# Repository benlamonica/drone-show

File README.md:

# drone-show
The code used for my amateur drone show quad-copters

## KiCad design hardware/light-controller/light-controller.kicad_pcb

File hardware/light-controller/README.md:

# Light controller

A 73 x 35 mm, 2-layer board that slides into the frame's light rail
(`frame/out/light_pcb_outline.dxf`). It hosts the Wi-Fi link and drives twelve 1 W-class
Cree XP-E2 LEDs (3 red, 3 green, 3 blue, 3 white) straight from a 4S-6S pack.

| | |
|---|---|
| MCU | RP2350A (QFN-60) + 2 MB W25Q16 flash, 12 MHz crystal |
| Wi-Fi | Raspberry Pi RM2 module (CYW43439), wired exactly like the Pico 2 W |
| LED drive | 4 x AL8860 hysteretic constant-current bucks, one per colour, 0.67 A each |
| LEDs | 12 x XP-E2 on the bottom side, facing the diffuser |
| Input | 4S-6S (12-26 V), reverse-polarity P-FET, SMBJ26A TVS |
| Logic supply | LMR51420 buck to 3.3 V |
| Interfaces | JST-SH UART to the flight controller, SWD and spares on 7 pogo-pin test pads |
| Board | 2 layers, 1.6 mm, 1 oz, smallest passive 0603, PCBWay standard rules |

## Files

| Path | What |
|---|---|
| `light-controller.kicad_pro/.kicad_sch/.kicad_pcb` | KiCad project (opens in KiCad 7 and later) |
| `light-controller.kicad_dru` | PCBWay design rules (loaded by DRC automatically) |
| `lightctl.kicad_sym`, `lightctl.pretty/` | Project-local symbols and footprints, nothing from global libraries |
| `fab/light-controller-gerbers.zip` | Upload this to PCBWay |
| `fab/light-controller-bom.csv`, `fab/light-controller-cpl.csv` | PCBWay assembly BOM and placement (both sides) |
| `images/` | Renders of both sides |
| `tools/` | The generators. `design.py` is the single source of the netlist and BOM |

Regenerate everything: `python3 tools/build_lib.py && python3 tools/gen_sch.py &&
python3 tools/gen_pcb.py`, then route (`tools/route.py`, `tools/finish_route.py`,
`tools/stitch.py`), check (`tools/drc.py`) and export (`tools/gen_fab.py`,
`tools/render.py`). Re-running `gen_pcb.py` throws the routing away, so after the
first build edit the board in KiCad instead.

## Brightness and power

Each colour is a string of three XP-E2 in series on its own AL8860, with the sense
resistor setting I = 0.1 V / 0.15 ohm = 0.67 A. At that current, roughly:

| Colour | Per LED | 3 LEDs |
|---|---|---|
| White (cool) | ~230 lm | ~700 lm |
| Green | ~170 lm | ~500 lm |
| Red | ~100 lm | ~300 lm |
| Blue | ~450 mW radiant | ~1.3 W radiant |

All four channels at full is about 1500 lm and 23 W into the LEDs, roughly 15-17 W of heat. Inside the diffuser the board sits in nearly still air, and a rough estimate is that it can shed only about 5 W continuously before the air inside passes 55-60 C, where a PLA diffuser starts to soften. These are estimates; measure on the bench (below) before setting final limits. The firmware must:

- hold the total LED power to about 5 W averaged over 30 s (roughly 150-200 lm of white, or one colour at about 75 %); short flashes above that are fine,
- read the NTC (`TH1`, on GPIO26), start dimming at 60 C board temperature and reach zero output at 80 C,
- never run full white on the bench without airflow.

The diffuser helps if it is printed in PETG or another plastic rated above 80 C instead of PLA, and if it has vent slots so prop wash moves air across the board (see `frame/`).

Bench test before building all 30: put one board in a diffuser, run it at a fixed power (start at 3 W, then 5 W, then 8 W) for 10 minutes each, and log the NTC temperature. The highest power that stays under 60 C is the real budget; update the numbers above with it.

To trade brightness for heat, change the four 0.15 ohm sense resistors
(`R31`-`R34`): 0.2 ohm gives 0.5 A. Don't go below 0.1 ohm (1 A, the XP-E2 maximum).

Dimming is PWM on each AL8860 CTRL pin through a 1k/10k divider. Keep the PWM under
500 Hz for linear dimming (1 kHz still works but the bottom of the range gets coarse).
CTRL below 0.2 V switches the channel fully off, so the LEDs are dark while the RP2350
is in reset. `C51`-`C54` are not fitted; fit them only to switch to analog dimming.

## Pin map

| GPIO | Function |
|---|---|
| 0 / 1 | UART TX / RX to the flight controller (MAVLink) |
| 2 | PWM green (PWM1 A) |
| 3 | PWM white (PWM1 B) |
| 8 | PWM red (PWM4 A) |
| 9 | PWM blue (PWM4 B) |
| 10, 11, 16 | Spare, on test pads TP2-TP4 |
| 23, 24, 25, 29 | RM2: WL_ON, data, CS, clock (same as Pico 2 W) |
| 26 (ADC0) | NTC board temperature |
| 27 (ADC1) | Battery voltage, 100k/10k divider (x11) |

Because the radio uses the Pico 2 W pins, the stock `pico2_w` board definition and
`pico_cyw43_arch` work unchanged. There is no separate status LED: use the CYW43
`WL_GPIO0` LED (`cyw43_arch_gpio_put(CYW43_WL_GPIO_LED_PIN, ...)`) as on a Pico 2 W, or
the main LEDs themselves. GPIO 4-7, 12-15, 17-22 and 28 are unconnected.

## Programming: pogo pins, no connectors

USB-C, the BOOTSEL button and the SWD connector were left off. All seven test pads sit in
one row on the bottom, 1.5 mm pads at 2.6 mm pitch along y = -13.4 mm, so one pogo-pin
jig reaches them all:

| Pad | x (mm) | Net |
|---|---|---|
| TP4 | -25.4 | GPIO16 |
| TP3 | -22.8 | GPIO11 |
| TP2 | -20.2 | GPIO10 |
| TP1 | -17.6 | RUN |
| TP5 | -15.0 | SWCLK |
| TP6 | -12.4 | GND |
| TP7 | -9.8 | SWDIO |

For the first flash, power the board from the pack and hold a Raspberry Pi Debug Probe
on TP5-TP7 (`openocd -f interface/cmsis-dap.cfg -f target/rp2350.cfg`). After that,
update the firmware over the flight controller UART or Wi-Fi.

Planned, not built yet: field updates use the RP2350 boot ROM's two-slot (A/B) partition
table instead of a custom bootloader. The running app receives a new image over the FC
UART (or Wi-Fi), writes it to the spare slot and reboots. If the new image doesn't
start, the boot ROM falls back to the old one, so a bad update can't brick a drone.

## Firmware port from the existing `pico/` code

The current firmware drives a WS2812B/SK6812 strip through `port/led_strip.c`. On this
board the same `led_strip_fill(r, g, b, w)` call should instead set four PWM levels on
GPIO 8, 2, 9, 3 (red, green, blue, white). The `show_led` MAVLink parser
(`DEBUG_VECT` "rgb") stays as it is. Use about 400 Hz PWM with a gamma table, and add
the power cap and NTC derating described above.

## Things to check before ordering

1. **XP-E2 polarity.** The footprint uses KiCad's `LED_Cree-XP` (pad 1 cathode, pad 2
   anode, centre pad 3 thermal and electrically neutral, tied to GND for heat). Compare
   with the current Cree XP-E2 datasheet drawing.
2. **RM2 footprint.** `RPi_RM2` was drawn from the RM2 datasheet (pads and antenna
   keep-out). Check it against the latest Raspberry Pi drawing; nothing may be placed
   under or in front of the antenna, and the board edge past it is clear of copper.
3. **ERC.** The schematic is generated, so open it in KiCad and run ERC once. The
   netlist was verified to match the board pin for pin.
4. **DRC.** Run DRC in KiCad with the project rules; see the routing notes below.
5. **LED bins.** Any in-stock flux bin works; the MPNs in the BOM are typical ones.

## Routing notes

The board was routed by script (Freerouting, then a grid router with rip-up in
`tools/finish_route.py`, then the `gnd_*` tools to tie every ground pad and pour island
together with stitching vias). Current DRC with `light-controller.kicad_dru`:

- 0 errors: no clearance, hole, width or unconnected items. The netlist on the board was
  checked pad by pad against `tools/design.py`.
- 76 silkscreen warnings (reference text overlapping other silk or clipped by the mask).
  They are cosmetic; tidy the reference text in KiCad if you care about the labels.

The tracks are machine-made and look it: there are short zig-zags and a few long
detours. They are electrically fine. Ground pads use solid (not thermal) pour
connections, so hand soldering ground pins needs a hot iron; reflow is unaffected.
The 0.4 mm-pitch RP2350 fan-out uses 0.15 mm tracks and 0.3/0.6 mm vias, inside
PCBWay's standard 6/6 mil, 0.3 mm process.

## PCBWay order settings

2 layers, FR-4, 1.6 mm, 1 oz outer copper, HASL lead-free or ENIG, min track/space
6/6 mil, min hole 0.3 mm. Assembly on both sides (LEDs, flash, buck and a few
passives are on the bottom). Battery leads are soldered by hand to `J1`.

## Main parts

| Ref | Part | Mouser / maker number |
|---|---|---|
| U2 | RP2350A | Raspberry Pi RP2350A (or RP2354A with built-in flash, then omit U3) |
| M1 | RM2 radio module | Raspberry Pi SC1169 |
| U3 | 16 Mbit QSPI flash | Winbond W25Q16JVSNIQ |
| U1 | 3.3 V buck | TI LMR51420YDDCR |
| L1 | 3.3 V buck inductor, 6.8 uH, 4 x 4 mm | Laird TYA40206R8M-10 (pads also fit Coilcraft XAL4020-682MEC) |
| U5-U8 | LED driver | Diodes AL8860MP-13 |
| L3-L6 | 47 uH 0.92 A | Bourns SRN6028-470M |
| D6-D9 | Schottky | Diodes B240A-13-F |
| R31-R34 | 0.15 ohm sense | Vishay WSL1206R1500FEA |
| LED1-12 | XP-E2 R/G/B/W | Cree XPEBRD, XPEBGR, XPEBBL, XPEBWT |
| Q1 | Reverse-polarity P-FET | Diodes DMP6023LE-13 |
| D2 | TVS | Littelfuse SMBJ26A |

The full list is in `fab/light-controller-bom.csv`.

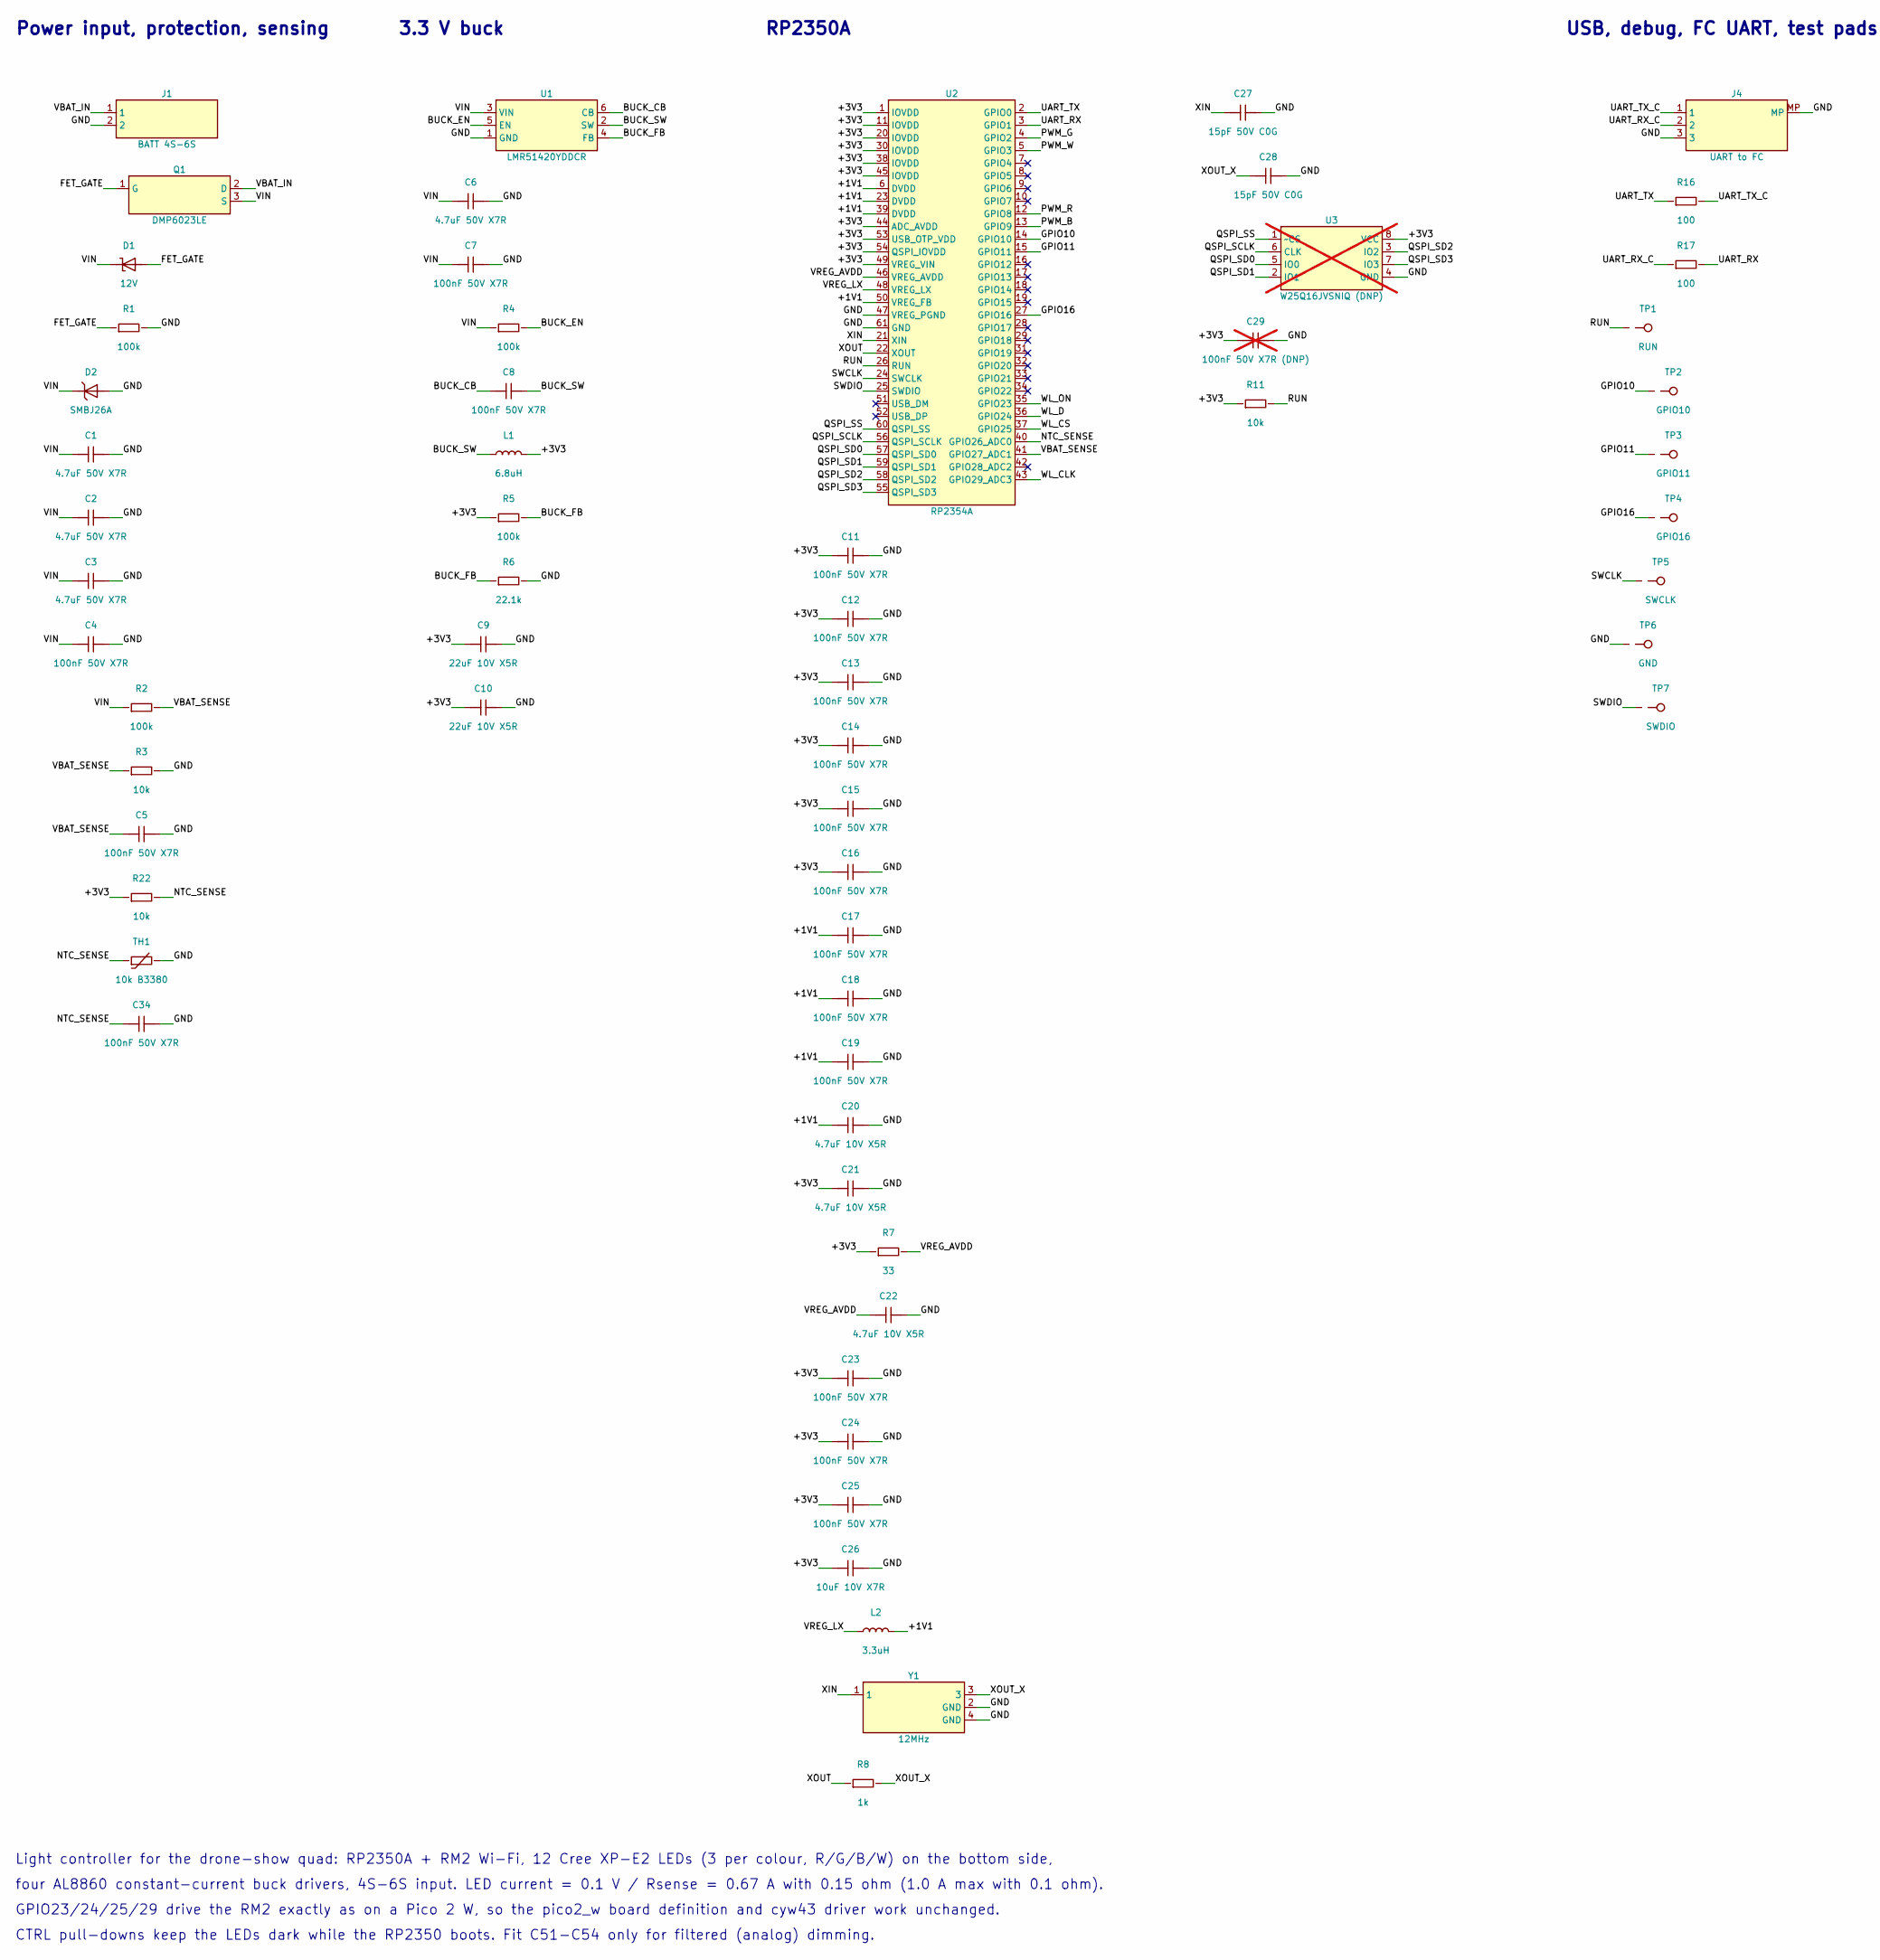
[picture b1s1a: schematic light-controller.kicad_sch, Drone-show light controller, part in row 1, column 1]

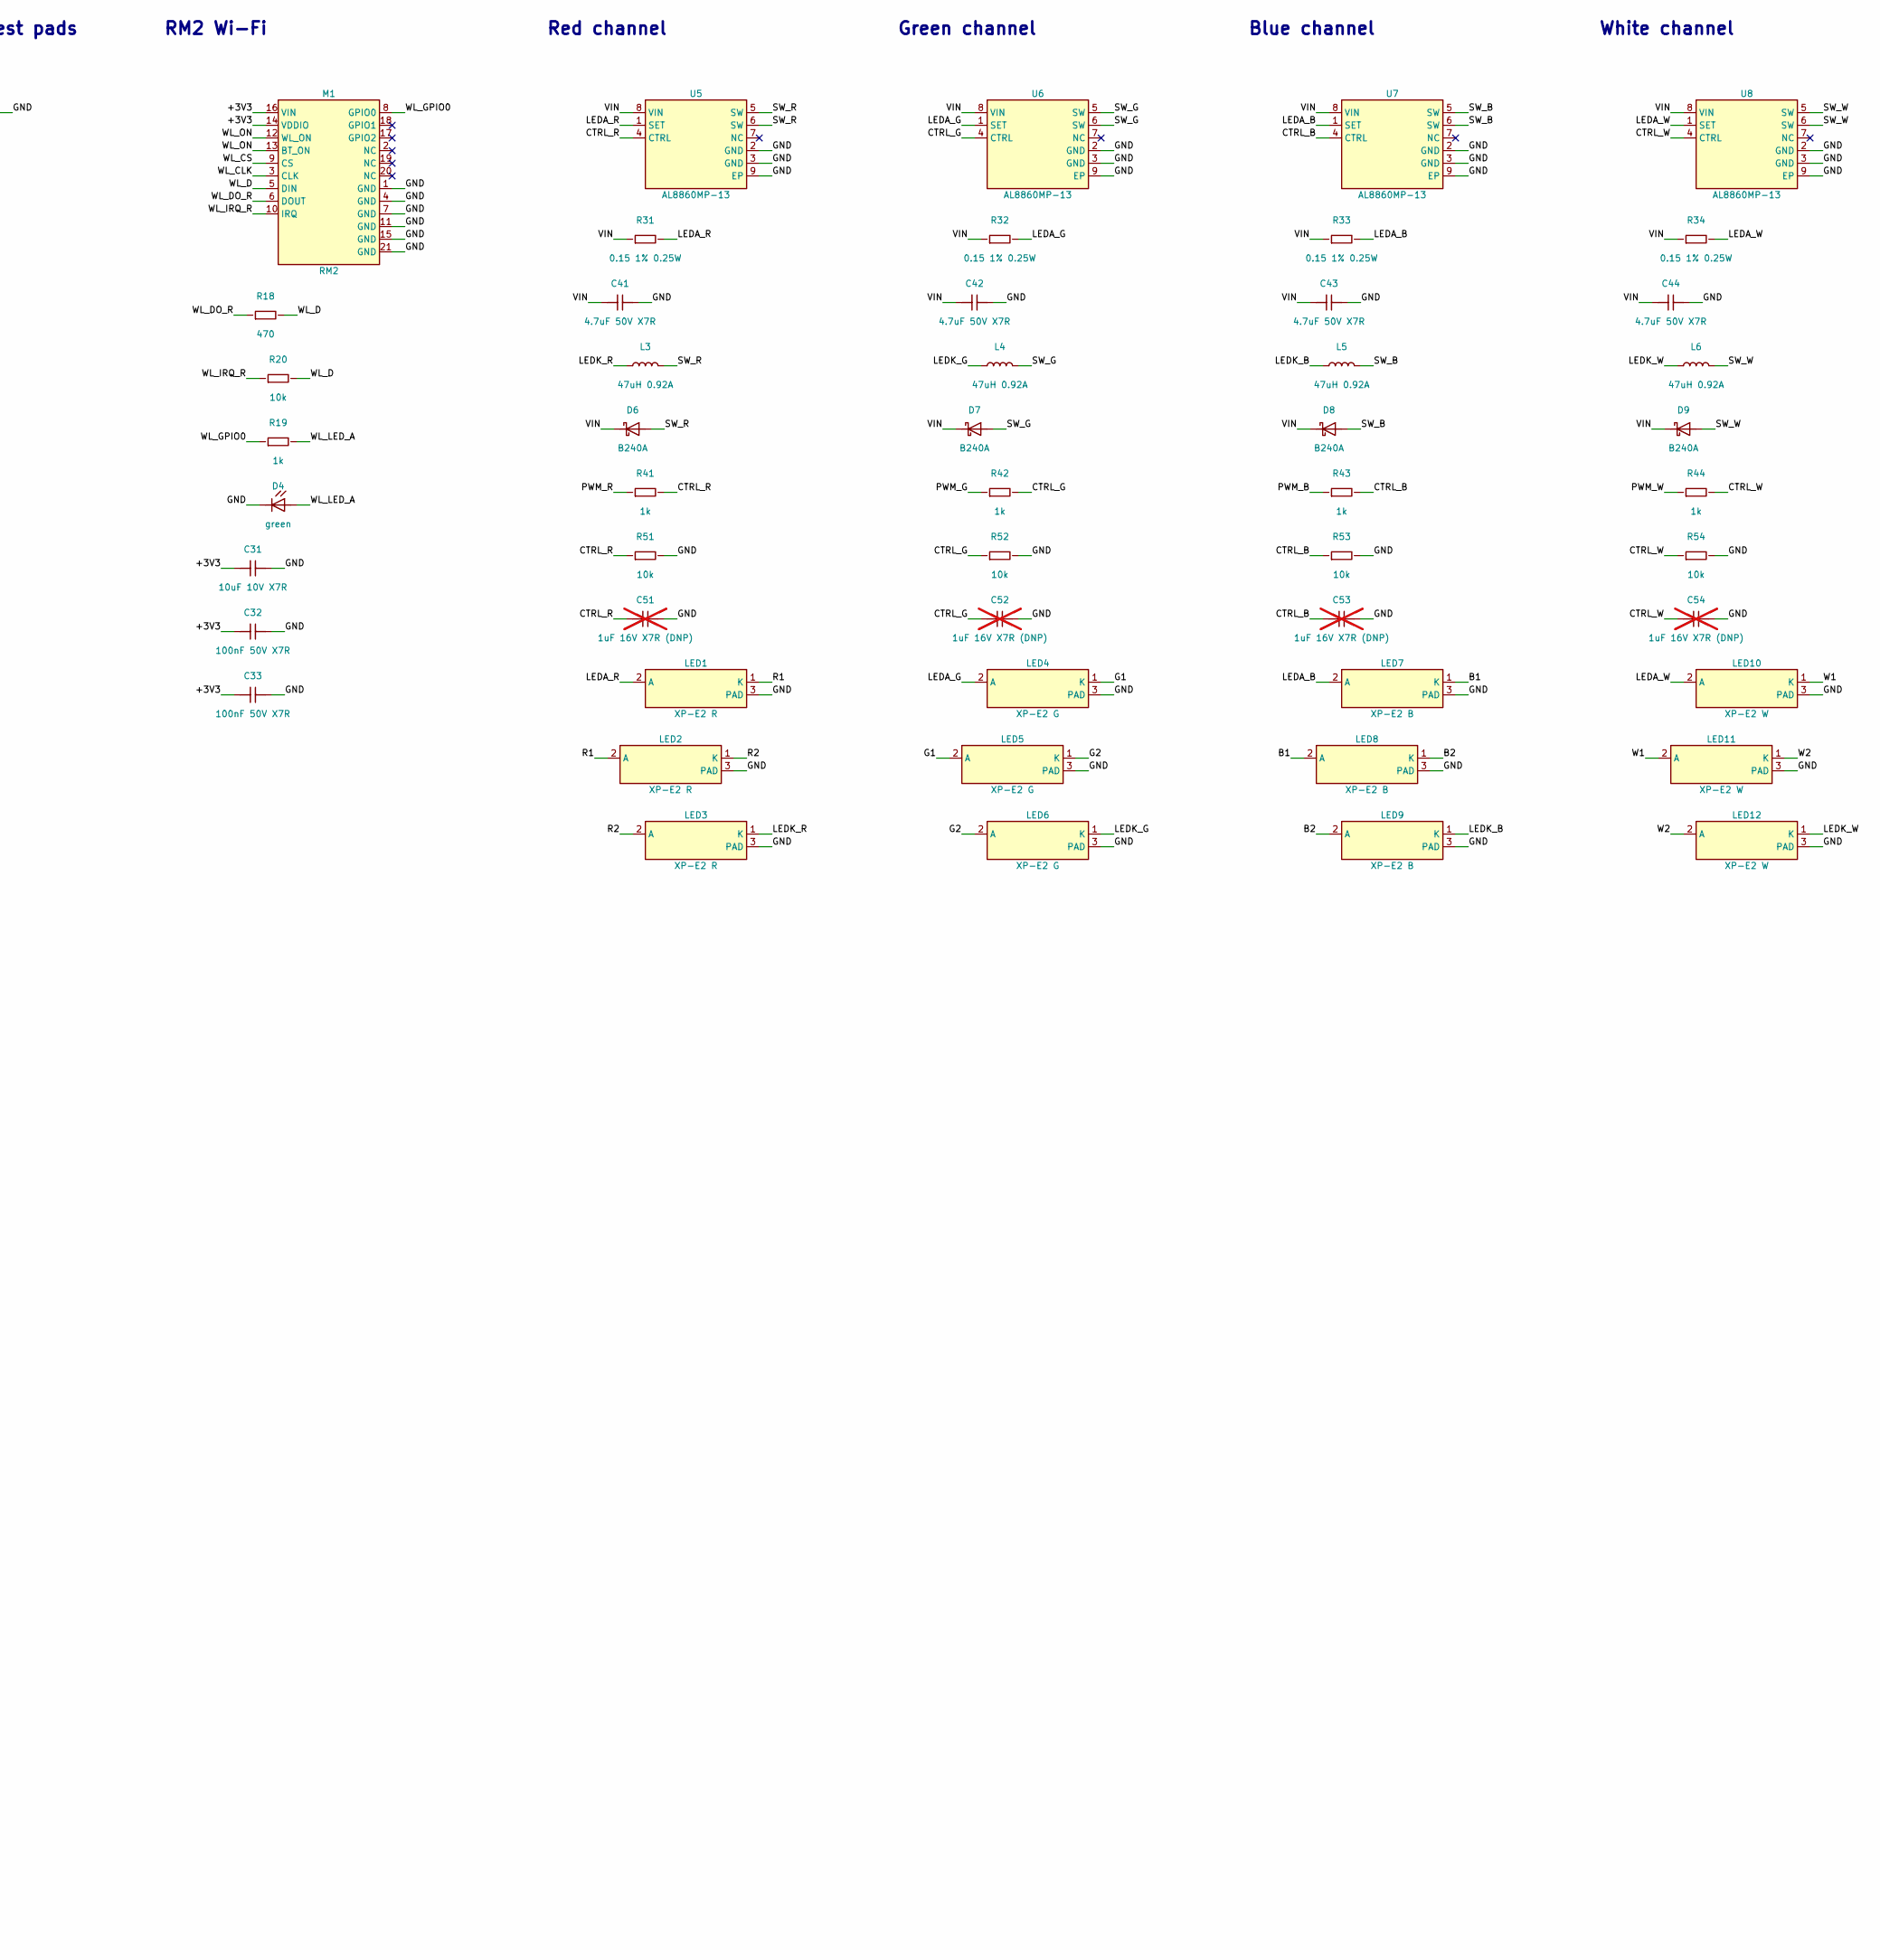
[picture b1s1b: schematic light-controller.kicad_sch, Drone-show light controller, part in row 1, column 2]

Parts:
C1, C2, C3, C6, C41, C42, C43, C44: 4.7uF 50V X7R; C_1206_3216Metric; MPN GRM31CR71H475KA12L
C4, C5, C7, C8, C11, C12, C13, C14, C15, C16, C17, C18, C19, C23, C24, C25, C32, C33, C34: 100nF 50V X7R; C_0603_1608Metric; MPN GRM188R71H104KA93D
C9, C10: 22uF 10V X5R; C_0805_2012Metric; MPN GRM21BR61A226ME44L
C20, C21, C22: 4.7uF 10V X5R; C_0603_1608Metric; MPN GRM188R61A475KE15D
C26, C31: 10uF 10V X7R; C_0805_2012Metric; MPN GRM21BR71A106KA73L
C27, C28: 15pF 50V C0G; C_0603_1608Metric; MPN GRM1885C1H150JA01D
C29: 100nF 50V X7R (DNP); C_0603_1608Metric; MPN GRM188R71H104KA93D; not fitted
C51, C52, C53, C54: 1uF 16V X7R (DNP); C_0603_1608Metric; MPN GRM188R71C105KA12D; not fitted
D1: 12V; D_SOD-123; MPN BZT52C12-7-F
D2: SMBJ26A; D_SMB; MPN SMBJ26A
D4: green; LED_0603_1608Metric; MPN 150060GS75000
D6, D7, D8, D9: B240A; D_SMA; MPN B240A-13-F
J1: BATT 4S-6S; SolderWire-0.5sqmm_1x02_P4.6mm_D0.9mm_OD2.1mm; MPN solder 20 AWG leads
J4: UART to FC; JST_SH_SM03B-SRSS-TB_1x03-1MP_P1.00mm_Horizontal; MPN SM03B-SRSS-TB(LF)(SN)
L1: 6.8uH; L_4020_XAL_TYA; MPN TYA40206R8M-10
L2: 3.3uH; L_Abracon_AOTA-B201610; MPN AOTA-B201610S3R3-101-T
L3, L4, L5, L6: 47uH 0.92A; L_Bourns-SRN6028; MPN SRN6028-470M
LED1, LED2, LED3: XP-E2 R; LED_Cree-XP; MPN XPEBRD-L1-0000-00801 (XP-E2 red, any in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
LED4, LED5, LED6: XP-E2 G; LED_Cree-XP; MPN XPEBGR-L1-0000-00E01 (XP-E2 green)
LED7, LED8, LED9: XP-E2 B; LED_Cree-XP; MPN XPEBBL-L1-0000-00Y01 (XP-E2 blue, any i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
LED10, LED11, LED12: XP-E2 W; LED_Cree-XP; MPN XPEBWT-L1-0000-00D50 (XP-E2 cool white)
M1: RM2; RPi_RM2; MPN SC1169 (Radio Module 2)
Q1: DMP6023LE; SOT-223-3_TabPin2; MPN DMP6023LE-13
R1, R2, R4, R5: 100k; R_0603_1608Metric; MPN RC0603FR-07100KL
R3, R11, R20, R22, R51, R52, R53, R54: 10k; R_0603_1608Metric; MPN RC0603FR-0710KL
R6: 22.1k; R_0603_1608Metric; MPN RC0603FR-0722K1L
R7: 33; R_0603_1608Metric; MPN RC0603FR-0733RL
R8, R19, R41, R42, R43, R44: 1k; R_0603_1608Metric; MPN RC0603FR-071KL
R16, R17: 100; R_0603_1608Metric; MPN RC0603FR-07100RL
R18: 470; R_0603_1608Metric; MPN RC0603FR-07470RL
R31, R32, R33, R34: 0.15 1% 0.25W; R_1206_3216Metric; MPN WSL1206R1500FEA
TH1: 10k B3380; R_0603_1608Metric; MPN NCP18XH103F03RB
TP1: RUN; TestPoint_Pad_D1.5mm; MPN test pad
TP2: GPIO10; TestPoint_Pad_D1.5mm; MPN test pad
TP3: GPIO11; TestPoint_Pad_D1.5mm; MPN test pad
TP4: GPIO16; TestPoint_Pad_D1.5mm; MPN test pad
TP5: SWCLK; TestPoint_Pad_D1.5mm; MPN test pad
TP6: GND; TestPoint_Pad_D1.5mm; MPN test pad
TP7: SWDIO; TestPoint_Pad_D1.5mm; MPN test pad
U1: LMR51420YDDCR; SOT-23-6; MPN LMR51420YDDCR
U2: RP2354A; RP2350A_QFN-60_7x7mm_P0.4mm; MPN RP2354A
U3: W25Q16JVSNIQ (DNP); SOIC-8_3.9x4.9mm_P1.27mm; MPN W25Q16JVSNIQ; not fitted
U5, U6, U7, U8: AL8860MP-13; MSOP-8-1EP_3x3mm_P0.65mm_EP1.68x1.88mm; MPN AL8860MP-13
Y1: 12MHz; Crystal_SMD_3225-4Pin_3.2x2.5mm; MPN ABM8-272-T3

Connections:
/+1V1: C17.1, C18.1, C19.1, C20.1, L2.2, U2.6 (DVDD), U2.23 (DVDD), U2.39 (DVDD), U2.50 (VREG_FB)
/+3V3: C9.1, C10.1, C11.1, C12.1, C13.1, C14.1, C15.1, C16.1, C21.1, C23.1, C24.1, C25.1, C26.1, C29.1, C31.1, C32.1, C33.1, L1.2, M1.14 (VDDIO), M1.16 (VIN), R5.1, R7.1, R11.1, R22.1, U2.1 (IOVDD), U2.11 (IOVDD), U2.20 (IOVDD), U2.30 (IOVDD), U2.38 (IOVDD), U2.44 (ADC_AVDD), U2.45 (IOVDD), U2.49 (VREG_VIN), U2.53 (USB_OTP_VDD), U2.54 (QSPI_IOVDD), U3.8 (VCC)
/B1: LED7.1 (K), LED8.2 (A)
/B2: LED8.1 (K), LED9.2 (A)
/BUCK_CB: C8.1, U1.6 (CB)
/BUCK_EN: R4.2, U1.5 (EN)
/BUCK_FB: R5.2, R6.1, U1.4 (FB)
/BUCK_SW: C8.2, L1.1, U1.2 (SW)
/CTRL_B: C53.1, R43.2, R53.1, U7.4 (CTRL)
/CTRL_G: C52.1, R42.2, R52.1, U6.4 (CTRL)
/CTRL_R: C51.1, R41.2, R51.1, U5.4 (CTRL)
/CTRL_W: C54.1, R44.2, R54.1, U8.4 (CTRL)
/FET_GATE: D1.2 (A), Q1.1 (G), R1.1
/G1: LED4.1 (K), LED5.2 (A)
/G2: LED5.1 (K), LED6.2 (A)
/GND: C1.2, C2.2, C3.2, C4.2, C5.2, C6.2, C7.2, C9.2, C10.2, C11.2, C12.2, C13.2, C14.2, C15.2, C16.2, C17.2, C18.2, C19.2, C20.2, C21.2, C22.2, C23.2, C24.2, C25.2, C26.2, C27.2, C28.2, C29.2, C31.2, C32.2, C33.2, C34.2, C41.2, C42.2, C43.2, C44.2, C51.2, C52.2, C53.2, C54.2, D2.2 (A), D4.1 (K), J1.2, J4.3, J4.MP, LED1.3 (PAD), LED2.3 (PAD), LED3.3 (PAD), LED4.3 (PAD), LED5.3 (PAD), LED6.3 (PAD), LED7.3 (PAD), LED8.3 (PAD), LED9.3 (PAD), LED10.3 (PAD), LED11.3 (PAD), LED12.3 (PAD), M1.1 (GND), M1.4 (GND), M1.7 (GND), M1.11 (GND), M1.15 (GND), M1.21 (GND), R1.2, R3.2, R6.2, R51.2, R52.2, R53.2, R54.2, TH1.2, TP6.1, U1.1 (GND), U2.47 (VREG_PGND), U2.61 (GND), U3.4 (GND), U5.2 (GND), U5.3 (GND), U5.9 (EP), U6.2 (GND), U6.3 (GND), U6.9 (EP), U7.2 (GND), U7.3 (GND), U7.9 (EP), U8.2 (GND), U8.3 (GND), U8.9 (EP), Y1.2 (GND), Y1.4 (GND); also elsewhere on the board
/GPIO10: TP2.1, U2.14 (GPIO10); also elsewhere on the board
/GPIO11: TP3.1, U2.15 (GPIO11); also elsewhere on the board
/GPIO16: TP4.1, U2.27 (GPIO16); also elsewhere on the board
/LEDA_B: LED7.2 (A), R33.2, U7.1 (SET)
/LEDA_G: LED4.2 (A), R32.2, U6.1 (SET)
/LEDA_R: LED1.2 (A), R31.2, U5.1 (SET)
/LEDA_W: LED10.2 (A), R34.2, U8.1 (SET)
/LEDK_B: L5.1, LED9.1 (K)
/LEDK_G: L4.1, LED6.1 (K)
/LEDK_R: L3.1, LED3.1 (K)
/LEDK_W: L6.1, LED12.1 (K)
/NTC_SENSE: C34.1, R22.2, TH1.1, U2.40 (GPIO26_ADC0)
/PWM_B: R43.1, U2.13 (GPIO9)
/PWM_G: R42.1, U2.4 (GPIO2)
/PWM_R: R41.1, U2.12 (GPIO8)
/PWM_W: R44.1, U2.5 (GPIO3)
/QSPI_SCLK: U2.56 (QSPI_SCLK), U3.6 (CLK)
/QSPI_SD0: U2.57 (QSPI_SD0), U3.5 (IO0)
/QSPI_SD1: U2.59 (QSPI_SD1), U3.2 (IO1)
/QSPI_SD2: U2.58 (QSPI_SD2), U3.3 (IO2)
/QSPI_SD3: U2.55 (QSPI_SD3), U3.7 (IO3)
/QSPI_SS: U2.60 (QSPI_SS), U3.1 (~CS)
/R1: LED1.1 (K), LED2.2 (A)
/R2: LED2.1 (K), LED3.2 (A)
/RUN: R11.2, TP1.1, U2.26 (RUN); also elsewhere on the board
/SWCLK: TP5.1, U2.24 (SWCLK); also elsewhere on the board
/SWDIO: TP7.1, U2.25 (SWDIO); also elsewhere on the board
/SW_B: D8.2 (A), L5.2, U7.5 (SW), U7.6 (SW)
/SW_G: D7.2 (A), L4.2, U6.5 (SW), U6.6 (SW)
/SW_R: D6.2 (A), L3.2, U5.5 (SW), U5.6 (SW)
/SW_W: D9.2 (A), L6.2, U8.5 (SW), U8.6 (SW)
/UART_RX: R17.2, U2.3 (GPIO1)
/UART_RX_C: J4.2, R17.1
/UART_TX: R16.1, U2.2 (GPIO0)
/UART_TX_C: J4.1, R16.2
/VBAT_IN: J1.1, Q1.2 (D)
/VBAT_SENSE: C5.1, R2.2, R3.1, U2.41 (GPIO27_ADC1)
/VIN: C1.1, C2.1, C3.1, C4.1, C6.1, C7.1, C41.1, C42.1, C43.1, C44.1, D1.1 (K), D2.1 (K), D6.1 (K), D7.1 (K), D8.1 (K), D9.1 (K), Q1.3 (S), R2.1, R4.1, R31.1, R32.1, R33.1, R34.1, U1.3 (VIN), U5.8 (VIN), U6.8 (VIN), U7.8 (VIN), U8.8 (VIN)
/VREG_AVDD: C22.1, R7.2, U2.46 (VREG_AVDD)
/VREG_LX: L2.1, U2.48 (VREG_LX)
/W1: LED10.1 (K), LED11.2 (A)
/W2: LED11.1 (K), LED12.2 (A)
/WL_CLK: M1.3 (CLK), U2.43 (GPIO29_ADC3)
/WL_CS: M1.9 (CS), U2.37 (GPIO25)
/WL_D: M1.5 (DIN), R18.2, R20.2, U2.36 (GPIO24)
/WL_DO_R: M1.6 (DOUT), R18.1
/WL_GPIO0: M1.8 (GPIO0), R19.1
/WL_IRQ_R: M1.10 (IRQ), R20.1
/WL_LED_A: D4.2 (A), R19.2
/WL_ON: M1.12 (WL_ON), M1.13 (BT_ON), U2.35 (GPIO23)
/XIN: C27.1, U2.21 (XIN), Y1.1
/XOUT: R8.1, U2.22 (XOUT)
/XOUT_X: C28.1, R8.2, Y1.3

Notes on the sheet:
Power input, protection, sensing
3.3 V buck
RP2350A
USB, debug, FC UART, test pads
RM2 Wi-Fi
Red channel
Green channel
Blue channel
White channel
Light controller for the drone-show quad: RP2350A + RM2 Wi-Fi, 12 Cree XP-E2 LEDs (3 per colour, R/G/B/W) on the bottom side,
four AL8860 constant-current buck drivers, 4S-6S input. LED current = 0.1 V / Rsense = 0.67 A with 0.15 ohm (1.0 A max with 0.1 ohm).
GPIO23/24/25/29 drive the RM2 exactly as on a Pico 2 W, so the pico2_w board definition and cyw43 driver work unchanged.
CTRL pull-downs keep the LEDs dark while the RP2350 boots. Fit C51-C54 only for filtered (analog) dimming.

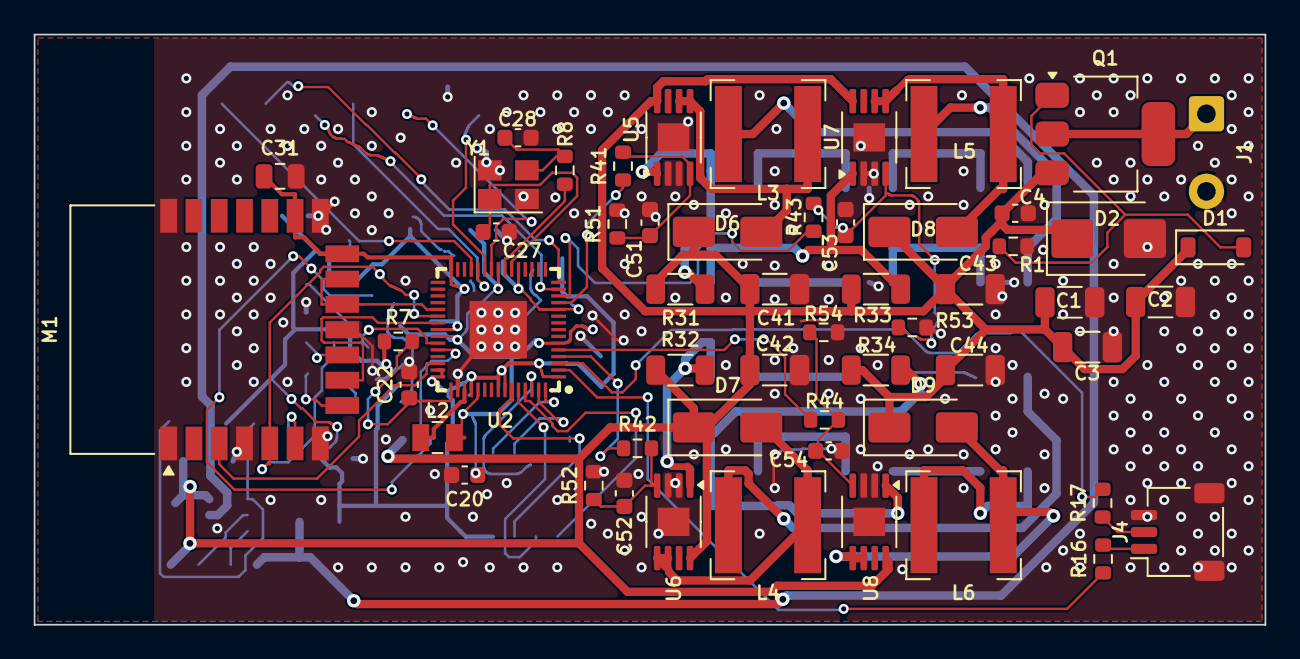
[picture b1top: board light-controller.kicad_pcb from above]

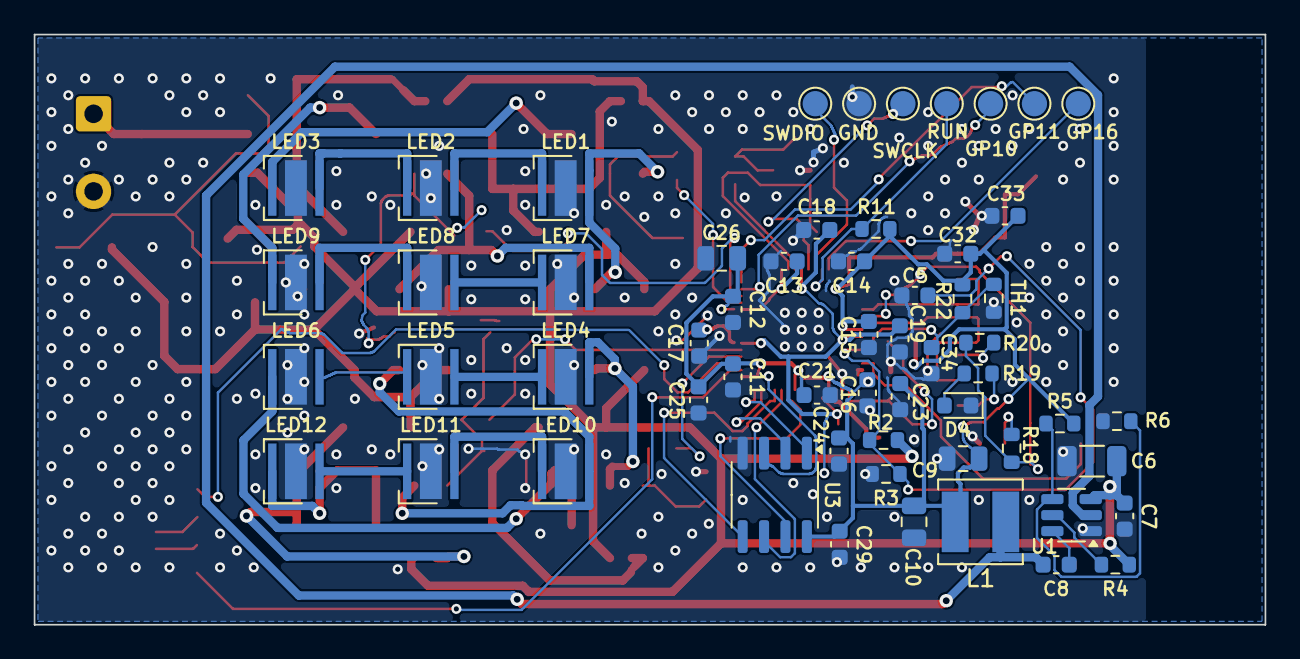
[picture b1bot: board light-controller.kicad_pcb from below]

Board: 2 copper layers, 73.0 x 35.0 mm, 113 parts (58 on the bottom side), 69 nets.

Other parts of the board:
GND: GND; TestPoint_Pad_D1.5mm
GP10: GPIO10; TestPoint_Pad_D1.5mm
GP11: GPIO11; TestPoint_Pad_D1.5mm
GP16: GPIO16; TestPoint_Pad_D1.5mm
RUN: RUN; TestPoint_Pad_D1.5mm
SWCLK: SWCLK; TestPoint_Pad_D1.5mm
SWDIO: SWDIO; TestPoint_Pad_D1.5mm

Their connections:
/GND: GND.1; also elsewhere on the board
/GPIO10: GP10.1; also elsewhere on the board
/GPIO11: GP11.1; also elsewhere on the board
/GPIO16: GP16.1; also elsewhere on the board
/RUN: RUN.1; also elsewhere on the board
/SWCLK: SWCLK.1; also elsewhere on the board
/SWDIO: SWDIO.1; also elsewhere on the board

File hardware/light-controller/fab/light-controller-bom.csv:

Item #,Designator,Qty,Manufacturer,Mfg Part #,Description / Value,Package/Footprint,Type,Your Instructions / Notes
1,J1,1,-,solder 20 AWG leads,BATT 4S-6S,SolderWire-0.5sqmm_1x02_P4.6mm_D0.9mm_OD2.1mm,THT/SMD,Do not place: battery leads soldered by hand
2,Q1,1,Diodes Inc,DMP6023LE-13,DMP6023LE,SOT-223-3_TabPin2,SMD,
3,D1,1,Diodes Inc,BZT52C12-7-F,12V,D_SOD-123,SMD,
4,R1 R2 R4 R5,4,Yageo,RC0603FR-07100KL,100k,R_0603_1608Metric,SMD,
5,D2,1,Littelfuse,SMBJ26A,SMBJ26A,D_SMB,SMD,
6,C1 C2 C3 C6 C41 C42 C43 C44,8,Murata,GRM31CR71H475KA12L,4.7uF 50V X7R,C_1206_3216Metric,SMD,
7,C4 C5 C7 C8 C11 C12 C13 C14 C15 C16 C17 C18 C19 C23 C24 C25 C32 C33 C34,19,Murata,GRM188R71H104KA93D,100nF 50V X7R,C_0603_1608Metric,SMD,
8,R3 R11 R20 R22 R51 R52 R53 R54,8,Yageo,RC0603FR-0710KL,10k,R_0603_1608Metric,SMD,
9,U1,1,Texas Instruments,LMR51420YDDCR,LMR51420YDDCR,SOT-23-6,SMD,
10,L1,1,Laird,TYA40206R8M-10,6.8uH,L_4020_XAL_TYA,SMD,
11,R6,1,Yageo,RC0603FR-0722K1L,22.1k,R_0603_1608Metric,SMD,
12,C9 C10,2,Murata,GRM21BR61A226ME44L,22uF 10V X5R,C_0805_2012Metric,SMD,
13,U2,1,Raspberry Pi,RP2354A,RP2354A,RP2350A_QFN-60_7x7mm_P0.4mm,SMD,
14,C20 C21 C22,3,Murata,GRM188R61A475KE15D,4.7uF 10V X5R,C_0603_1608Metric,SMD,
15,R7,1,Yageo,RC0603FR-0733RL,33,R_0603_1608Metric,SMD,
16,C26 C31,2,Murata,GRM21BR71A106KA73L,10uF 10V X7R,C_0805_2012Metric,SMD,
17,L2,1,Abracon,AOTA-B201610S3R3-101-T,3.3uH,L_Abracon_AOTA-B201610,SMD,
18,Y1,1,Abracon,ABM8-272-T3,12MHz,Crystal_SMD_3225-4Pin_3.2x2.5mm,SMD,
19,R8 R19 R41 R42 R43 R44,6,Yageo,RC0603FR-071KL,1k,R_0603_1608Metric,SMD,
20,C27 C28,2,Murata,GRM1885C1H150JA01D,15pF 50V C0G,C_0603_1608Metric,SMD,
21,J4,1,JST,SM03B-SRSS-TB(LF)(SN),UART to FC,JST_SH_SM03B-SRSS-TB_1x03-1MP_P1.00mm_Horizontal,SMD,
22,R16 R17,2,Yageo,RC0603FR-07100RL,100,R_0603_1608Metric,SMD,
23,TP1,1,-,test pad,RUN,TestPoint_Pad_D1.5mm,SMD,"Bare pad, nothing to place"
24,TP2,1,-,test pad,GPIO10,TestPoint_Pad_D1.5mm,SMD,"Bare pad, nothing to place"
25,TP3,1,-,test pad,GPIO11,TestPoint_Pad_D1.5mm,SMD,"Bare pad, nothing to place"
26,TP4,1,-,test pad,GPIO16,TestPoint_Pad_D1.5mm,SMD,"Bare pad, nothing to place"
27,TP5,1,-,test pad,SWCLK,TestPoint_Pad_D1.5mm,SMD,"Bare pad, nothing to place"
28,TP6,1,-,test pad,GND,TestPoint_Pad_D1.5mm,SMD,"Bare pad, nothing to place"
29,TP7,1,-,test pad,SWDIO,TestPoint_Pad_D1.5mm,SMD,"Bare pad, nothing to place"
30,M1,1,Raspberry Pi,SC1169 (Radio Module 2),RM2,RPi_RM2,SMD,
31,R18,1,Yageo,RC0603FR-07470RL,470,R_0603_1608Metric,SMD,
32,D4,1,Wurth Elektronik,150060GS75000,green,LED_0603_1608Metric,SMD,
33,TH1,1,Murata,NCP18XH103F03RB,10k B3380,R_0603_1608Metric,SMD,
34,U5 U6 U7 U8,4,Diodes Inc,AL8860MP-13,AL8860MP-13,MSOP-8-1EP_3x3mm_P0.65mm_EP1.68x1.88mm,SMD,
35,R31 R32 R33 R34,4,Vishay Dale,WSL1206R1500FEA,0.15 1% 0.25W,R_1206_3216Metric,SMD,
36,L3 L4 L5 L6,4,Bourns,SRN6028-470M,47uH 0.92A,L_Bourns-SRN6028,SMD,
37,D6 D7 D8 D9,4,Diodes Inc,B240A-13-F,B240A,D_SMA,SMD,
38,LED1 LED2 LED3,3,Cree LED,"XPEBRD-L1-0000-00801 (XP-E2 red, any in-stock flux bin)",XP-E2 R,LED_Cree-XP,SMD,Bottom side. Any in-stock flux bin of this colour.
39,LED4 LED5 LED6,3,Cree LED,XPEBGR-L1-0000-00E01 (XP-E2 green),XP-E2 G,LED_Cree-XP,SMD,Bottom side. Any in-stock flux bin of this colour.
40,LED7 LED8 LED9,3,Cree LED,"XPEBBL-L1-0000-00Y01 (XP-E2 blue, any in-stock flux bin)",XP-E2 B,LED_Cree-XP,SMD,Bottom side. Any in-stock flux bin of this colour.
41,LED10 LED11 LED12,3,Cree LED,XPEBWT-L1-0000-00D50 (XP-E2 cool white),XP-E2 W,LED_Cree-XP,SMD,Bottom side. Any in-stock flux bin of this colour.

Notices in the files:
hardware/flight-controller/show-fc.kicad_sch:
Derived from OpenFC-Lite rev3.3 (CERN-OHL-S-2.0)
